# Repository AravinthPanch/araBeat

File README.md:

# araBeat

araBeat is an interactive new media art developed for the artistic sonification of Electrocardiogram (ECG). It is a complete system that consists of modules of ECG, DSP, MCU & Motherboard.

araBeat captures ECG of human Interactors through two gel-less electrodes, identifies the QRS complex of ECG, calculates the time difference between the R wave peaks and using Audio DSP, it synthesizes high & low frequency sound in realtime, which is synchronized with the heartbeats of the Interactor.

araBeat lies in the spectrum of new media art, the form of interaction with the technology is designed with aesthetics in mind using stainless steel electrodes in the form of human hand.

araBeat is designed to be extendable using modular designs, so that every component can be just individually plugged into the motherboard. It is also built as an industrial grade system to operate in harsh weather conditions from -40 ° Celsius to 85 ° Celsius. Furthermore, it is designed to comply with medical grade electronics to have low electrical noises and safety.

In the first public appearance, araBeat is integrated into a permanent & public mosaic art installation called "The Heart Of Uptown", located at MoZaic East, Minneapolis, USA.

<p align="center">
<b>The Heart Of Uptown powered by araBeat</b>
</br>
</br>

</p>

## ARTISTS

-   Aravinth Panch &lt; <http://aravinth.info> > New Media Art
-   Stacia Goodman &lt; <http://www.staciagoodmanmosaics.com> > Mosaic Art

## COLLABORATORS

-   Marc Basara - Project Management, Minneapolis
-   Stuart Ackerberg - Art Producer, Minneapolis
-   Felix Christmann - Industrial Design, Berlin
-   Alessandro Aresta - Sound Engineering, Berlin
-   Len Goodman - Graphic Design, Minneapolis
-   John Bean, Giam Nguyen, Hart Johnson, Randi Johnson - Production Management, Minneapolis
-   Pavel Spieker, Kelly Ludeking, Anthony Kling - Structural Design & Construction, Minneapolis
-   Shresth Agrawal - Software Engineering, Berlin
-   Chris Kooper - Metalworking, Berlin

## SUPPORTERS

-   Natalia Aravinth, Mladen Miljic, Darina Onoprienko - Family & Mental Support
-   David Riding, Jasmin Skenderi - Electrical Design Review, Next Big Thing, Berlin
-   Karissa Xie, Rolin Pei - CNC Machining, HLH Prototypes, Shenzhen
-   Monica Shen, Ivy Li, Carmen Zheng - PCB Manufacturing, Seeed Studio, Shenzhen
-   Goran, Sascha Hamacher - WaterJet Cutting, S-Hamacher Art Production Studio, Berlin
-   Robert Blowsky - Digital Signal Processing, Analog Devices, EZ Forum

## STUDIOS AND MANUFACTURERS

-   nLab, Berlin - Interaction Technology Design & Development
-   MotionLab, Berlin - Prototype CNC Machining
-   Tivoli Too, Minneapolis - Structural Design & Construction
-   Seeed Studio, Shenzhen - PCB Manufacturing
-   Troublemaker, Shenzhen - Prototyping
-   HLH Prototypes, Shenzhen - CNC Machining
-   S-Hamacher Art Production Studio, Berlin - WaterJet Cutting & Metalworking

## DESIGN

### Interaction Technology & Mosaic Installation Concept

## DEVELOPMENT

### The Heart Of Uptown Installation

-   #### Stage 1 Completion

-   #### Stage 2 Completion

-   #### Stage 3 Completion

### Interaction Technology

-   #### Wiring Design

-   #### Prototype v1.0

-   #### Prototype v2.0

-   #### Prototype v3.0

-   #### Prototype v4.0

-   #### Motherboard v0.1

<p align="center">

</br>

</p>

-   #### ECG Module v0.1

-   #### ECG Module v0.2

-   #### MCU Module v0.1

-   #### Motherboard v1.0

<p align="center">

</br>

</p>

-   #### Motherboard v1.0 in Weatherproof Industrial Heated Enclosure

### Sensor Frontend

-   #### Design

-   #### Prototype

-   #### Sensor Frontend v1.0

#### Marine Standard Tweeter, Sub-Woofer, Amplifier, PSU

#### Electronics & Audio Chambers

## DESIGN & DEVELOPMENT TOOLS

-   #### KiCad v5.0.1-3 for PCB Design

-   #### Atom v1.34.0 + Platform IO v4.0.0a3 for ECG Firmware Development

-   #### Fusion 360 v2.0.5357 for Mechanical Design

-   #### Rhino + Grasshoper for Surface Design

-   #### Affinity Designer v1.6.1 for Vector Design

-   #### SigmaStudio v4.2 for Audio Synthesis

-   #### Processing v3.5.3 for araBeat GUI Software Development

-   #### araBeat GUI v0.9 for Optimisation of ECG and Audio Waveforms

## The Making - Behind the scenes

-   #### Aravinth - Prototype CNC Milling at MotionLab, Berlin

-   #### Stacia - Mosaic Making at Private Studio, Minneapolis

-   #### Stacia - Mosaic Making at Private Studio, Minneapolis

-   #### Len - Structural Construction at Tivoli Too, Minneapolis

-   #### Stacia - Styrofoam + Fibreglass Surface Finish at Tivoli Too, Minneapolis

-   #### Len - Mosaic Finish at Tivoli Too, Minneapolis

-   #### Alessandro - Sound Design at Private Studio, Berlin

-   #### Chris - Metalworking at S-Hamacher Art Production Studio, Berlin

-   #### Pavel - Metalworking at Tivoli Too, Minneapolis

-   #### Kelly - Metalworking at Tivoli Too, Minneapolis

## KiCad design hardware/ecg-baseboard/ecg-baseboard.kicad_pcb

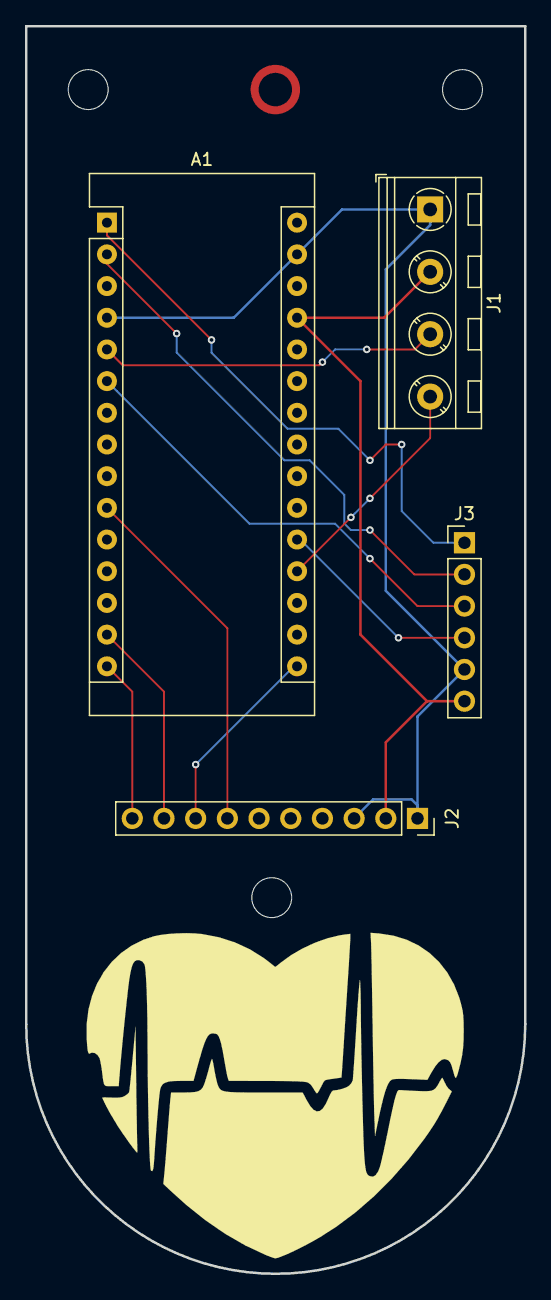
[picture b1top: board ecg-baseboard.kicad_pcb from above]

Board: 2 copper layers, 40.0 x 100.0 mm, 4 parts (0 on the bottom side), 12 nets.

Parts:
A1: Arduino_Nano_v3.x; Arduino_Nano
J1: Screw_Terminal_01x04; TerminalBlock_RND_205-00047_1x04_P5.00mm_Horizontal
J2: Protocentral MAX30003; PinSocket_1x10_P2.54mm_Vertical
J3: Conn_01x06; PinHeader_1x06_P2.54mm_Vertical

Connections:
/VCC: A1.27, J1.2, J2.2, J3.6
GND: A1.4, A1.29, J1.1, J2.1, J2.3, J3.5
unnamed: A1.1, J3.1
unnamed: A1.2, J3.2
unnamed: A1.5, J1.3
unnamed: A1.6, J3.3
unnamed: A1.10, J2.7
unnamed: A1.14, J2.9
unnamed: A1.15, J2.10
unnamed: A1.16, J2.8
unnamed: A1.19, J1.4
unnamed: A1.20, J3.4

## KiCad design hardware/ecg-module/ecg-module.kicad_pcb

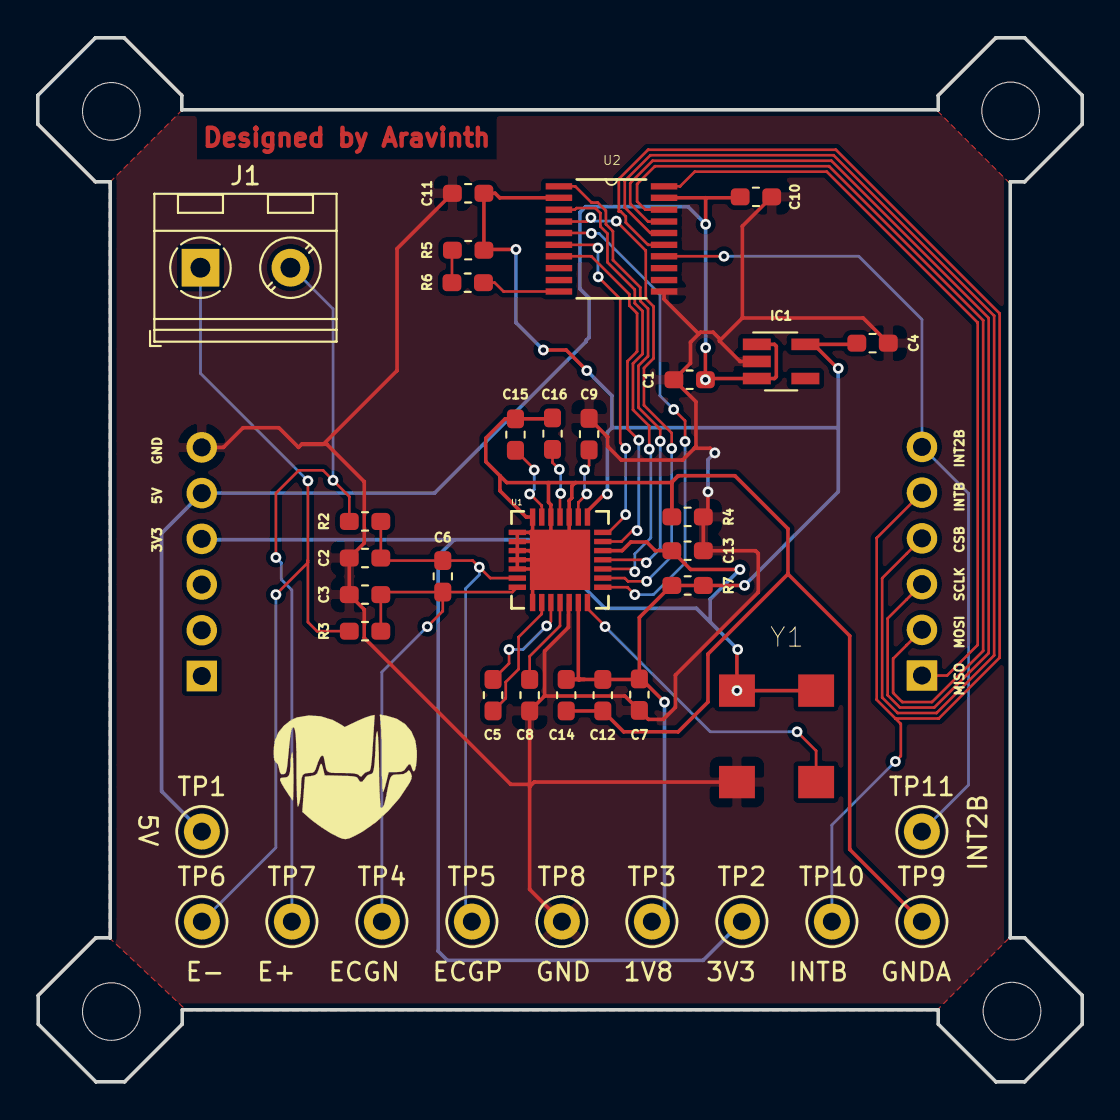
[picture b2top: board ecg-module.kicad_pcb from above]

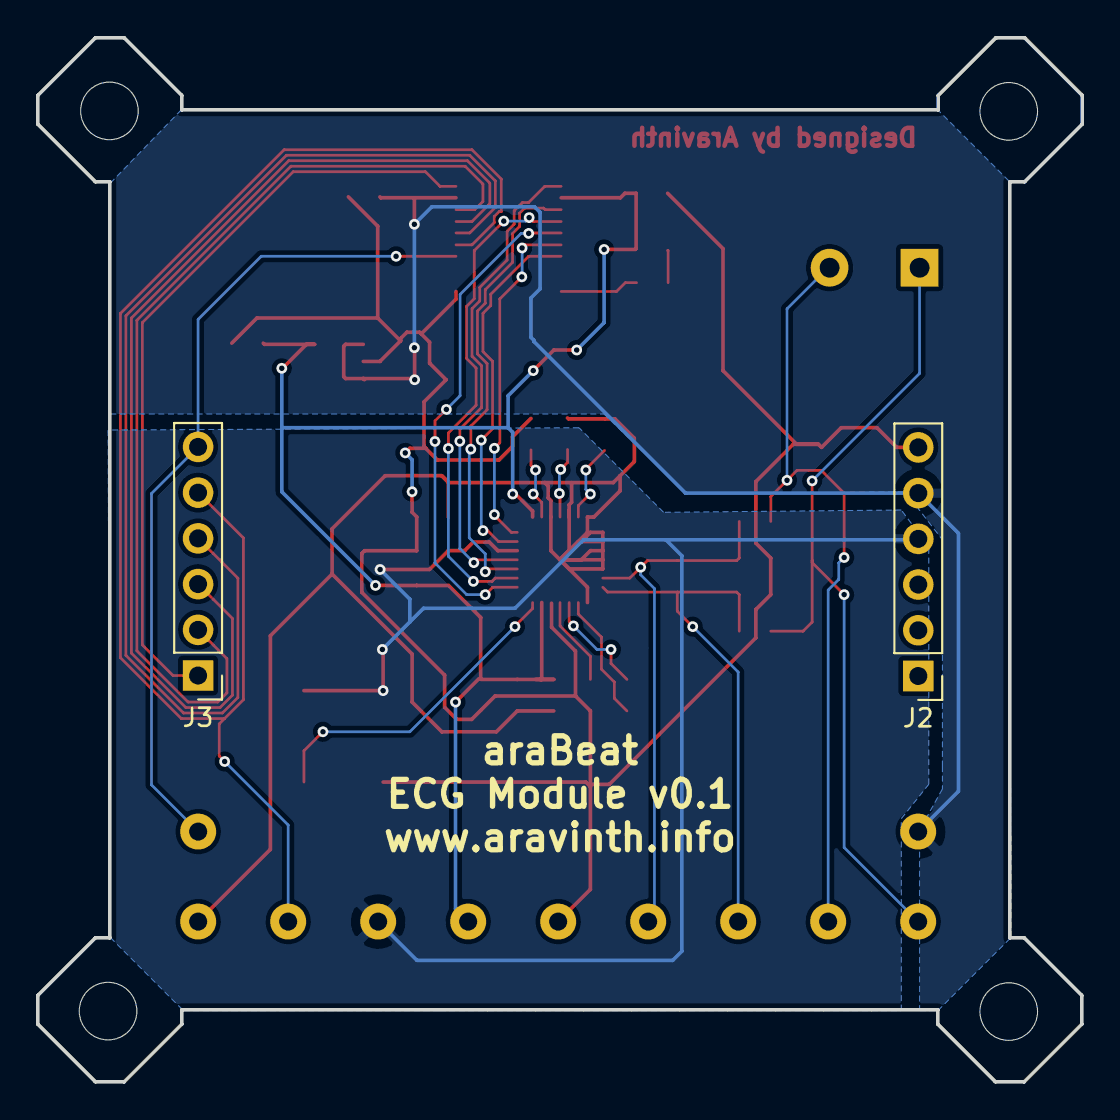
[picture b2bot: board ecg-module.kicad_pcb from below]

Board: 2 copper layers, 58.0 x 58.0 mm, 40 parts (2 on the bottom side), 30 nets.

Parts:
C1, C4, C5, C7, C12, C15: 1uF; C_0603_1608Metric_Pad1.05x0.95mm_HandSolder
C2, C3: 10pF; C_0603_1608Metric_Pad1.05x0.95mm_HandSolder
C6, C8: 1000pF; C_0603_1608Metric_Pad1.05x0.95mm_HandSolder
C9, C13, C16: 10uF; C_0603_1608Metric_Pad1.05x0.95mm_HandSolder
C10, C11, C14: 0.1uF; C_0603_1608Metric_Pad1.05x0.95mm_HandSolder
IC1: AP2112K-1.8TRG1; SOT-23-5_HandSoldering
J1: ST_01x02; TerminalBlock_RND_205-00045_1x02_P5.00mm_Horizontal
J2: LEFT-UI; PinHeader_1x06_P2.54mm_Vertical
J3: RIGHT-UI; PinHeader_1x06_P2.54mm_Vertical
R2, R3: 49.9K; R_0603_1608Metric_Pad1.05x0.95mm_HandSolder
R4, R5, R7: 0R; R_0603_1608Metric_Pad1.05x0.95mm_HandSolder
R6: 10K; R_0603_1608Metric_Pad1.05x0.95mm_HandSolder
TP1: 5V; TestPoint_Keystone_5000-5004_Miniature
TP2: 3V3; TestPoint_Keystone_5000-5004_Miniature
TP3: 1V8; TestPoint_Keystone_5000-5004_Miniature
TP4: ECGN; TestPoint_Keystone_5000-5004_Miniature
TP5: ECGP; TestPoint_Keystone_5000-5004_Miniature
TP6: E-; TestPoint_Keystone_5000-5004_Miniature
TP7: E+; TestPoint_Keystone_5000-5004_Miniature
TP8: GND; TestPoint_Keystone_5000-5004_Miniature
TP9: GNDA; TestPoint_Keystone_5000-5004_Miniature
TP10: INTB; TestPoint_Keystone_5000-5004_Miniature
TP11: INT2B; TestPoint_Keystone_5000-5004_Miniature
U1: 21-0140L_T2855-8
U2: SOP65P640X120-20N
Y1: OSCSC508P500X700X155-4N

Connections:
+1V8: C4.1, C7.1, C11.2, C12.1, C14.1, IC1.5, R5.2, R7.1, R7.2, TP3.1, U1.13, U1.22, U2.2
+3V3: C13.1, J2.4, TP2.1, U1.19, Y1.1, Y1.4
+5V: C1.1, C10.2, IC1.1, IC1.3, J2.5, TP1.1, U2.19
CSB_1.8V: U1.15, U2.5
CSB_5V: J3.4, U2.16
GND: C1.2, C2.1, C3.2, C4.2, C7.2, C8.2, C9.2, C10.1, C11.1, C13.2, IC1.2, J2.6, R4.2, TP8.1, U1.12, U2.11, Y1.2
GNDA: C12.2, C14.2, C15.2, C16.2, R4.1, TP9.1, U1.1, U1.2, U1.3, U1.4, U1.5, U1.8, U1.24, U1.26, U1.28, U1.29
INT2B_1.8V: U1.20, U2.7
INT2B_5V: J3.6, TP11.1, U2.14
INTB_1.8V: U1.21, U2.6
INTB_5V: J3.5, TP10.1, U2.15
MISO_1.8V: U1.18, U2.1
MISO_5V: J3.1, U2.20
MOSI_1.8V: U1.17, U2.3
MOSI_5V: J3.2, U2.18
unnamed: C2.2, C6.2, R2.1, TP5.1, U1.6
unnamed: C3.1, C6.1, R3.1, TP4.1, U1.7
unnamed: C5.1, U1.9
unnamed: C5.2, U1.10
unnamed: C8.1, U1.11
unnamed: C9.1, U1.23
unnamed: C15.1, U1.27
unnamed: C16.1, U1.25
unnamed: J1.1, R3.2, TP6.1
unnamed: J1.2, R2.2, TP7.1
unnamed: R5.1, R6.2
unnamed: R6.1, U2.10
unnamed: U1.14, Y1.3
SCLK_1.8V: U1.16, U2.4
SCLK_5V: J3.3, U2.17

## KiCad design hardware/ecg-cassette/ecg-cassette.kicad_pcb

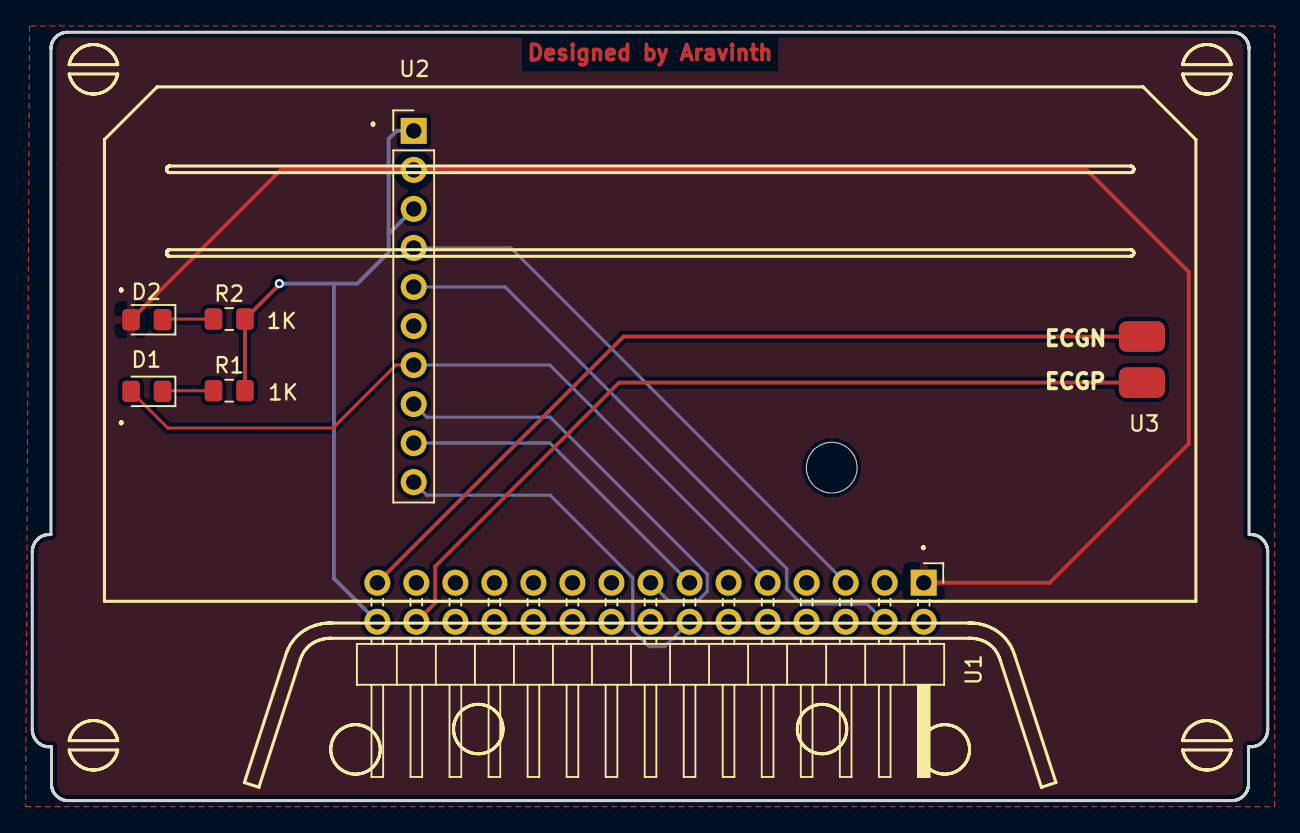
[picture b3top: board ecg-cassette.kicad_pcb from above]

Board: 2 copper layers, 80.4 x 50.0 mm, 9 parts (0 on the bottom side), 12 nets.

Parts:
D1: RED_STATUS_LED; LED_0805_2012Metric_Pad1.15x1.40mm_HandSolder
D2: GREEN_PWR_LED; LED_0805_2012Metric_Pad1.15x1.40mm_HandSolder
MARK: CASSETTE-MARK; MCU-CASSETTE-MARK
R1, R2: 1K; R_0805_2012Metric_Pad1.15x1.40mm_HandSolder
SILK: CASSETTE-SILKSCREEN; ECG-CASSETTE-SILKSCREEN-EDGECUT
U1: 02x15_PIN_HEADER_SOCKET; PinHeader_2x15_P2.54mm_Horizontal
U2: MAX30003
U3: ECG-WIRE-TO-BOARD

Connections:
5V: D2.2, U1.1, U2.2
D2: U1.4, U2.5
D3: U1.5, U2.4
D7: D1.2, U1.9, U2.7
D11: U1.13, U2.9
D12: U1.14, U2.10
D13: U1.15, U2.8
ECGN: U1.29, U3.1
ECGP: U1.28, U3.2
GND: R1.2, R2.2, U1.30, U2.1, U2.3
unnamed: D1.1, R1.1
unnamed: D2.1, R2.1

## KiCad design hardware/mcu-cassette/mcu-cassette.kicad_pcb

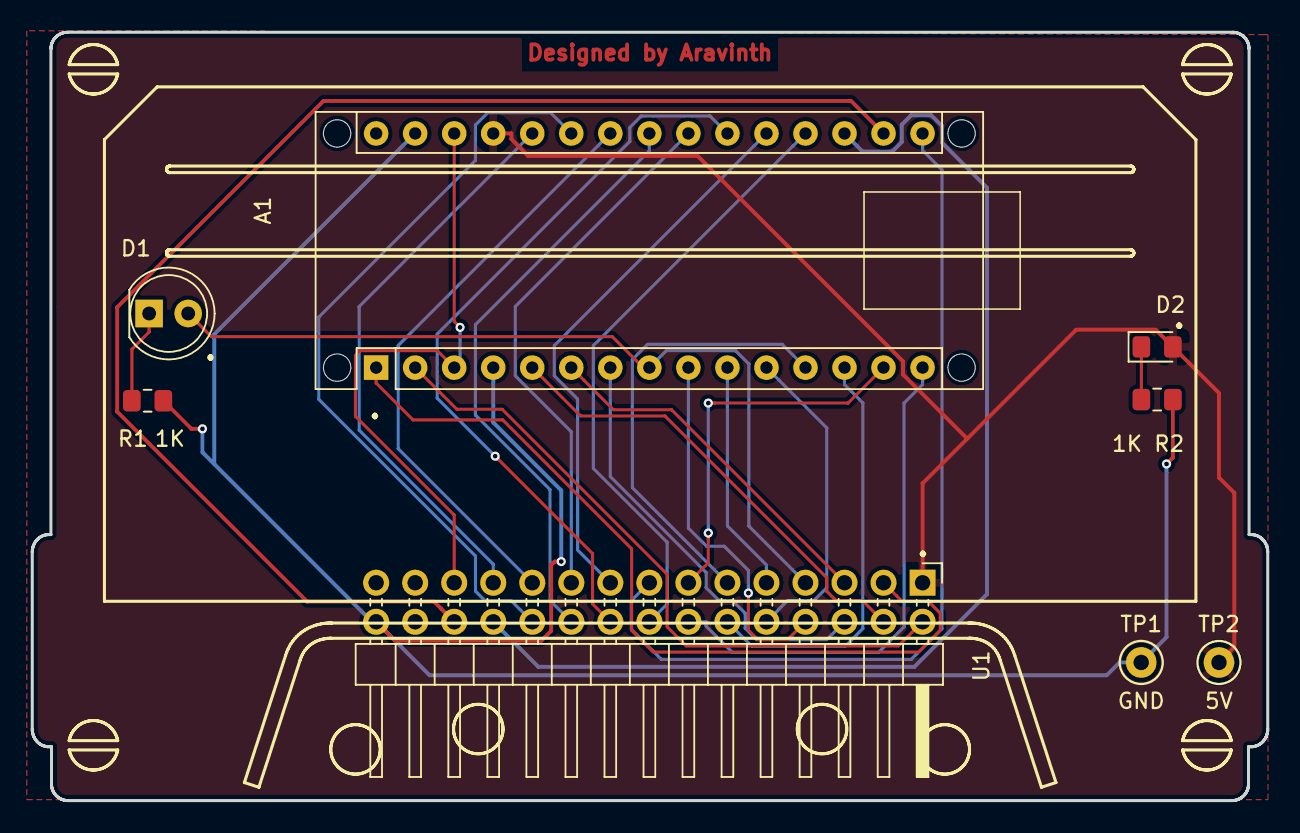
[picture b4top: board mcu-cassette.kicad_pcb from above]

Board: 2 copper layers, 80.4 x 50.0 mm, 10 parts (0 on the bottom side), 29 nets.

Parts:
A1: Arduino_Nano_v3.x; Arduino_Nano_WithMountingHoles
D1: RED_HEART_LED; LED_D5.0mm
D2: GREEN_PWR_LED; LED_0805_2012Metric_Pad1.15x1.40mm_HandSolder
R1, R2: 1K; R_0805_2012Metric_Pad1.15x1.40mm_HandSolder
SLK-FR: CASSETTE-SILKSCREEN; MCU-CASSETTE-SILKSCREEN-EDGECUT
SLK-MK: CASSETTE-MARK; MCU-CASSETTE-MARK
TP1: GND; TestPoint_Keystone_5000-5004_Miniature
TP2: 5V; TestPoint_Keystone_5000-5004_Miniature
U1: 02x15_PIN_HEADER_SOCKET; PinHeader_2x15_P2.54mm_Horizontal

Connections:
3V3: A1.17, U1.26
5V: A1.27, D2.2, TP2.1, U1.1
A0: A1.19, U1.16
A1: A1.20, U1.17
A2: A1.21, U1.18
A3: A1.22, U1.19
A4: A1.23, U1.20
A5: A1.24, U1.21
A6: A1.25, U1.22
A7: A1.26, U1.23
AREF: A1.18, U1.24
D0: A1.2, U1.2
D1: A1.1, U1.3
D2: A1.5, U1.4
D3: A1.6, U1.5
D4: A1.7, U1.6
D5: A1.8, D1.2, U1.7
D6: A1.9, U1.8
D7: A1.10, U1.9
D8: A1.11, U1.10
D9: A1.12, U1.11
D10: A1.13, U1.12
D11: A1.14, U1.13
D12: A1.15, U1.14
D13: A1.16, U1.15
GND: A1.4, A1.29, R1.2, R2.2, TP1.1, U1.30
unnamed: D1.1, R1.1
unnamed: D2.1, R2.1
RST: A1.3, A1.28, U1.25

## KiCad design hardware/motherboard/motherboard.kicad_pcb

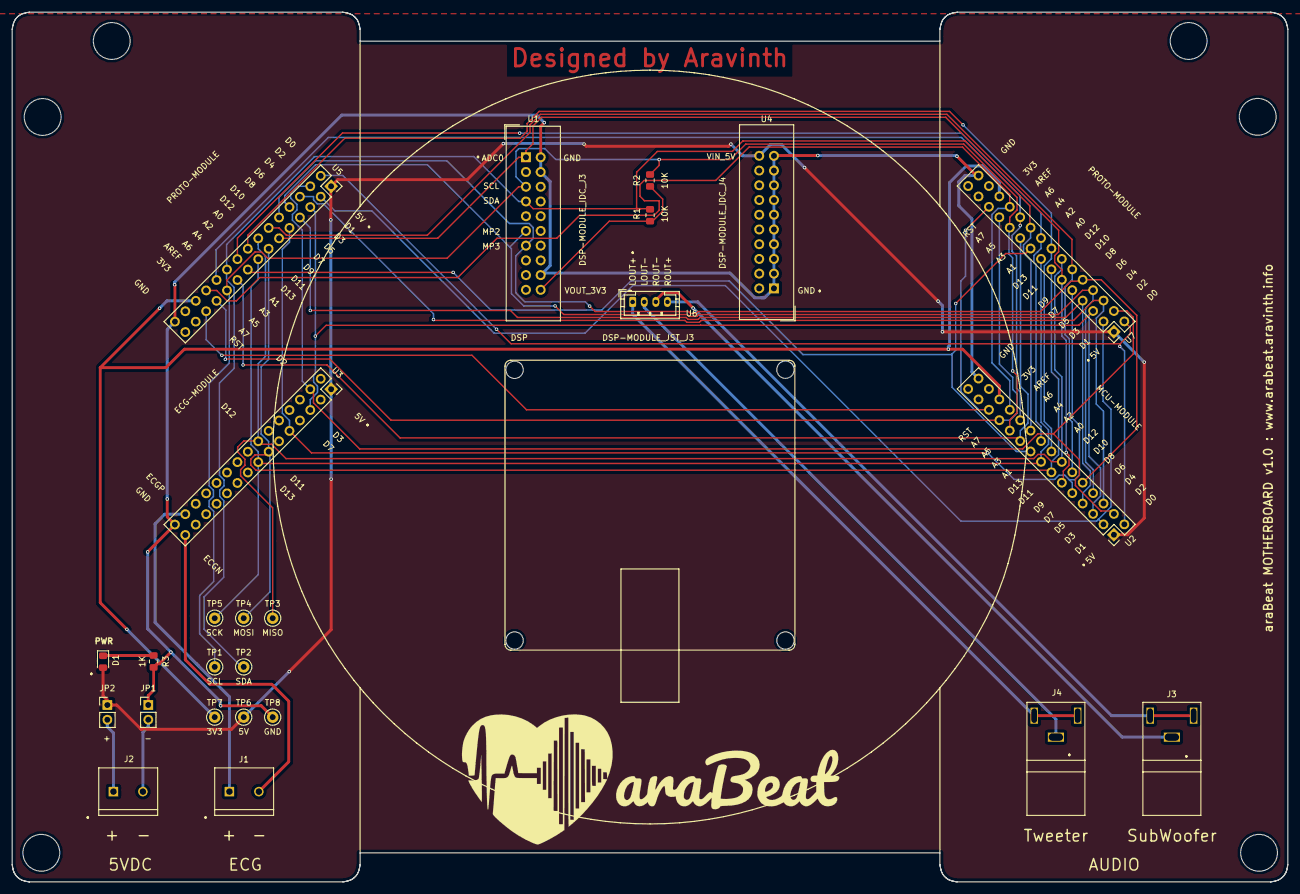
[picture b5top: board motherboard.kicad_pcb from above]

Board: 2 copper layers, 220.0 x 150.0 mm, 27 parts (0 on the bottom side), 37 nets.

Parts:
D1: GREEN_PWR_LED; LED_0805_2012Metric_Pad1.15x1.40mm_HandSolder
DSP: WONDOM-DSP
J1: 01x02_Screw_ECG; 282837-2
J2: 01x02_Screw_5VDC_IN; 282837-2
J3: RCA_L_Female_Tweeter; PJRAN1X1U01X
J4: RCA_R_Female_Sub; PJRAN1X1U01X
JP1: GND_Jumper; 382811-8
JP2: 5V_Jumper; 382811-8
MOTHERBOARD: MOTHERBOARD-SILKSCREEN-EDGECUT-MARK
R1, R2: 10K; R_0805_2012Metric_Pad1.15x1.40mm_HandSolder
R3: 1K; R_0805_2012Metric_Pad1.15x1.40mm_HandSolder
TP1: SCL; TestPoint_Keystone_5000-5004_Miniature
TP2: SDA; TestPoint_Keystone_5000-5004_Miniature
TP3: MISO; TestPoint_Keystone_5000-5004_Miniature
TP4: MOSI; TestPoint_Keystone_5000-5004_Miniature
TP5: SCK; TestPoint_Keystone_5000-5004_Miniature
TP6: 5V; TestPoint_Keystone_5000-5004_Miniature
TP7: 3V3; TestPoint_Keystone_5000-5004_Miniature
TP8: GND; TestPoint_Keystone_5000-5004_Miniature
U1: DSP-MODULE_IDC_J3; IDC-Header_2x10_P2.54mm_Vertical
U2: MCU-MODULE; PinSocket_2x15_P2.54mm_Vertical
U3: ECG-MODULE; PinSocket_2x15_P2.54mm_Vertical
U4: DSP-MODULE_IDC_J4; IDC-Header_2x10_P2.54mm_Vertical
U5, U7: PROTO-MODULE; PinSocket_2x15_P2.54mm_Vertical
U6: DSP-MODULE_JST_J3; JST_PH_B4B-PH-K_1x04_P2.00mm_Vertical

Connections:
3V3: TP7.1, U2.26, U5.26, U7.26
5V: D1.2, JP2.1, TP6.1, U2.1, U3.1, U4.20, U5.1, U7.1
A0: U2.16, U5.16, U7.16
A1: U2.17, U5.17, U7.17
A2: U2.18, U5.18, U7.18
A3: U2.19, U5.19, U7.19
A4: R1.2, TP2.1, U1.7, U2.20, U5.20, U7.20
A5: R2.2, TP1.1, U1.5, U2.21, U5.21, U7.21
A6: U2.22, U5.22, U7.22
A7: U2.23, U5.23, U7.23
AREF: U2.24, U5.24, U7.24
D0: U2.2, U5.2, U7.2
D1: U2.3, U5.3, U7.3
D2: U2.4, U3.4, U5.4, U7.4
D3: U2.5, U3.5, U5.5, U7.5
D4: U2.6, U5.6, U7.6
D5: U2.7, U5.7, U7.7
D6: U1.11, U2.8, U5.8, U7.8
D7: U2.9, U3.9, U5.9, U7.9
D8: U1.13, U2.10, U5.10, U7.10
D9: U1.1, U2.11, U5.11, U7.11
D10: U2.12, U5.12, U7.12
D11: TP4.1, U2.13, U3.13, U5.13, U7.13
D12: TP3.1, U2.14, U3.14, U5.14, U7.14
D13: TP5.1, U2.15, U3.15, U5.15, U7.15
ECGN: J1.2, U3.29
ECGP: J1.1, U3.28
GND: JP1.1, R3.2, TP8.1, U1.2, U1.4, U1.18, U2.30, U3.30, U4.1, U4.3, U4.5, U4.7, U4.9, U4.11, U4.13, U4.15, U4.17, U4.19, U5.30, U7.30
LOUT+: J4.2, J4.3, U6.1
LOUT-: J4.1, U6.2
unnamed: D1.1, R3.1
unnamed: J2.1, JP2.2
unnamed: J2.2, JP1.2
unnamed: R1.1, R2.1, U1.20
ROUT+: J3.2, J3.3, U6.4
ROUT-: J3.1, U6.3
RST: U2.25, U5.25, U7.25

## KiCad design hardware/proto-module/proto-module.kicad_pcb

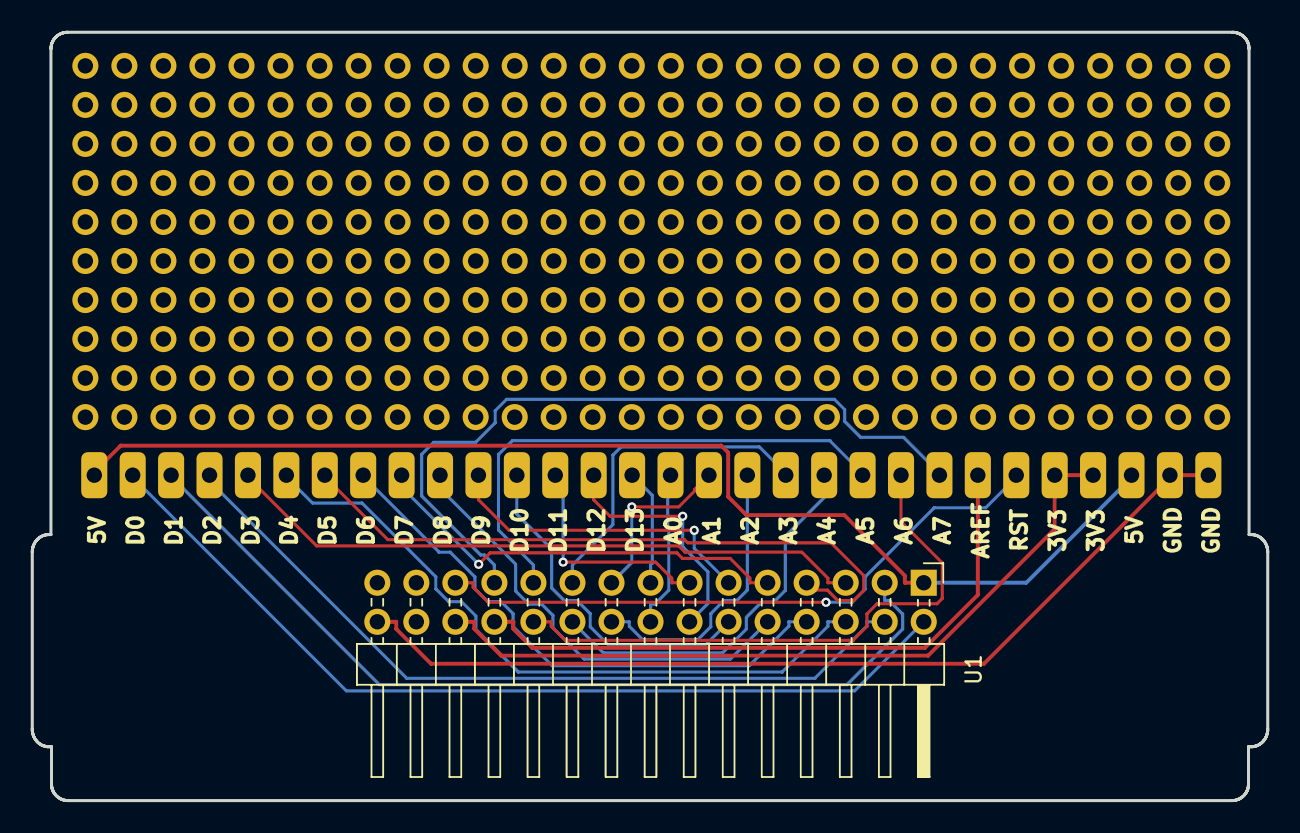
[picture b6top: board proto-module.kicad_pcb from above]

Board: 2 copper layers, 80.4 x 50.0 mm, 3 parts (0 on the bottom side), 27 nets.

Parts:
J1: Conn_01x30; PERF-PADS
PERF: PERF-BOARD
U1: 02x15_PIN_HEADER_SOCKET; PinHeader_2x15_P2.54mm_Horizontal

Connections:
3V3: J1.26, J1.27, U1.26
5V: J1.1, J1.28, U1.1
A0: J1.16, U1.16
A1: J1.17, U1.17
A2: J1.18, U1.18
A3: J1.19, U1.19
A4: J1.20, U1.20
A5: J1.21, U1.21
A6: J1.22, U1.22
A7: J1.23, U1.23
AREF: J1.24, U1.24
D0: J1.2, U1.2
D1: J1.3, U1.3
D2: J1.4, U1.4
D3: J1.5, U1.5
D4: J1.6, U1.6
D5: J1.7, U1.7
D6: J1.8, U1.8
D7: J1.9, U1.9
D8: J1.10, U1.10
D9: J1.11, U1.11
D10: J1.12, U1.12
D11: J1.13, U1.13
D12: J1.14, U1.14
D13: J1.15, U1.15
GND: J1.29, J1.30, U1.30
RST: J1.25, U1.25

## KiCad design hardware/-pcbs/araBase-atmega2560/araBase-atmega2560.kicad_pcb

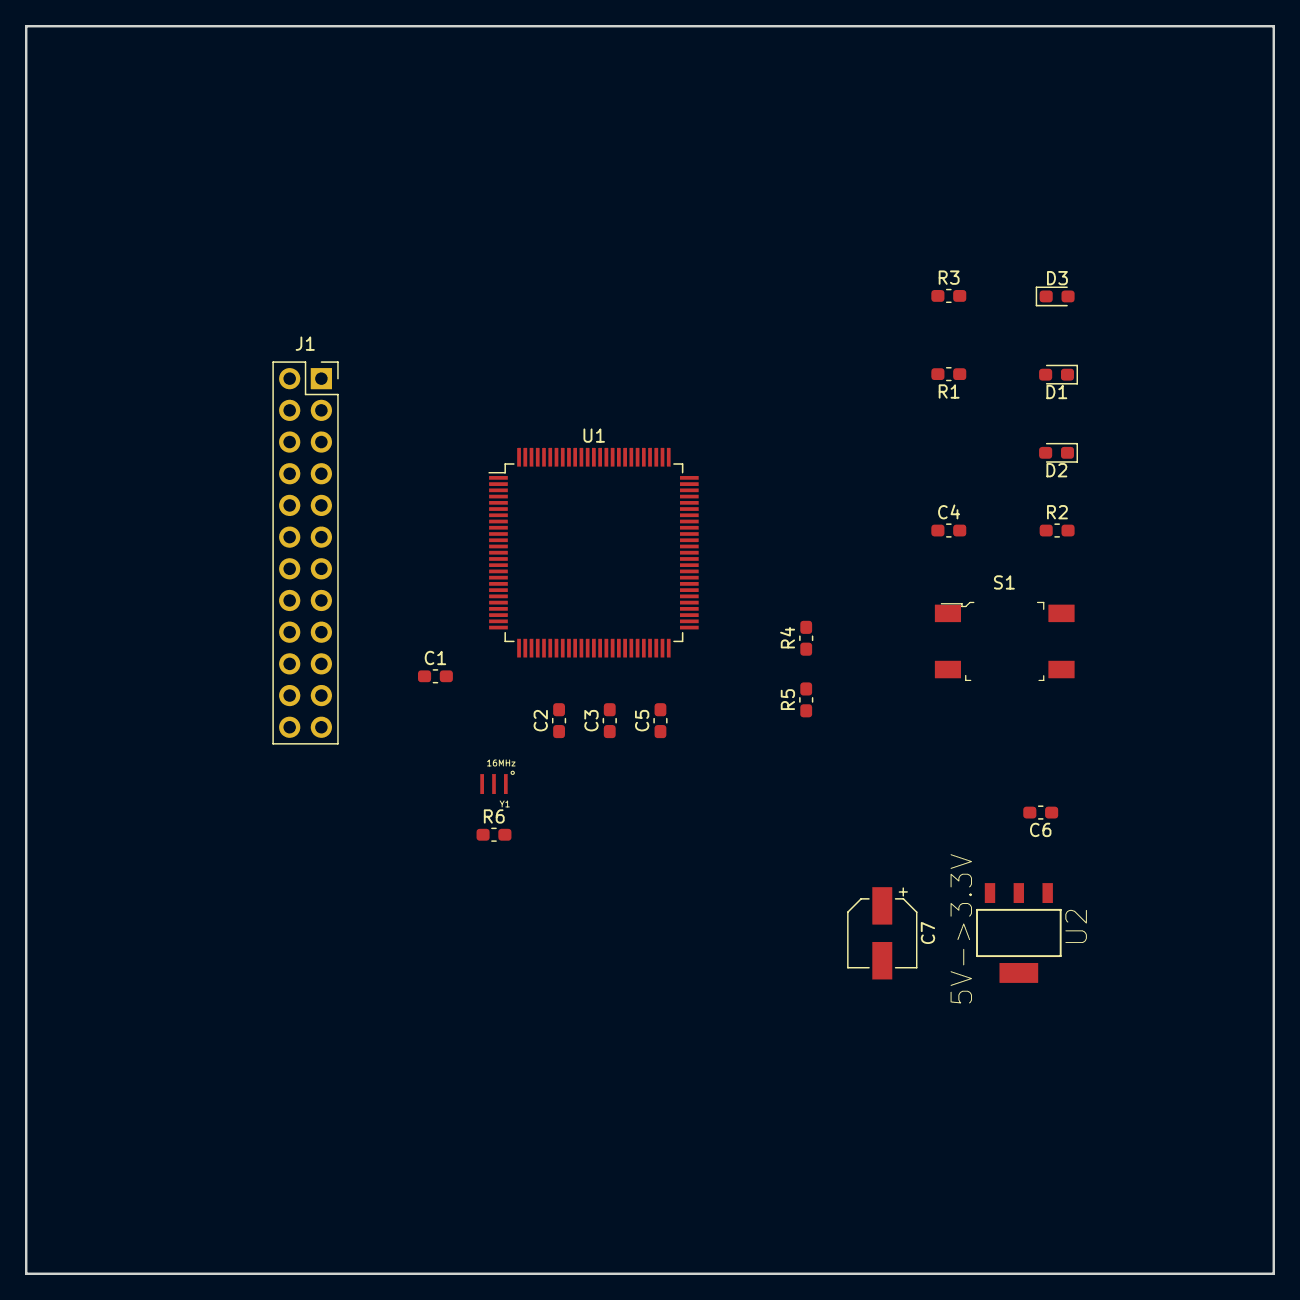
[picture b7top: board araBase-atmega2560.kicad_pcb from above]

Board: 2 copper layers, 100.0 x 100.0 mm, 21 parts (0 on the bottom side), 30 nets, no tracks yet.

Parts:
C1, C2, C3, C5: 0.1uF; C_0603_1608Metric_Pad1.05x0.95mm_HandSolder
C4: 22pF; C_0603_1608Metric_Pad1.05x0.95mm_HandSolder
C6: 100nF; C_0603_1608Metric_Pad1.05x0.95mm_HandSolder
C7: 33uF; CP_Elec_5x5.8
D1: LED-Y; LED_0603_1608Metric_Pad1.05x0.95mm_HandSolder
D2: 100V; D_0603_1608Metric_Pad1.05x0.95mm_HandSolder
D3: LED-G; LED_0603_1608Metric_Pad1.05x0.95mm_HandSolder
J1: UI; PinSocket_2x12_P2.54mm_Vertical
R1, R2, R3, R4, R5: 10K; R_0603_1608Metric_Pad1.05x0.95mm_HandSolder
R6: 1M; R_0603_1608Metric_Pad1.05x0.95mm_HandSolder
S1: RESET-SW; Switch_Tactile_SMD_6x6mm
U1: ATmega2560-16AU; TQFP-100_14x14mm_P0.5mm
U2: 5V->3.3V; SOT230P696X180-4N
Y1: 16MHz; OSC_CSTCE16M0V53-R0

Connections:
+5V: C2.1, C3.1, C5.1, C6.1, D2.1, J1.1, R2.2, R3.1, R4.2, R5.2, U1.10, U1.31, U1.61, U1.80, U1.100, U2.1
/3.3V: C7.1, J1.3, U2.3
/A0: J1.13, U1.97
/A1: J1.14, U1.96
/A2: J1.15, U1.95
/A3: J1.16, U1.94
/A4: J1.17, U1.93
/A5: J1.18, U1.92
/AREF: C1.1, J1.12, U1.98
/D2: J1.19, U1.6
/D3: J1.20, U1.7
/D4: J1.21, U1.1
/D5: J1.22, U1.5
/D6: J1.23, U1.15
/D7: J1.24, U1.16
/MISO: J1.6, U1.22
/MOSI: J1.7, U1.21
/RESET: C4.1, D2.2, J1.4, R2.1
/RX0: J1.9, U1.2
/SCK: J1.5, U1.20
/SCL: J1.11, R4.1, U1.43
/SDA: J1.10, R5.1, U1.44
/TX0: J1.8, U1.3
GND: C1.2, C2.2, C3.2, C4.2, C5.2, C6.2, C7.2, D1.1, D3.1, J1.2, S1.1, S1.2, U1.11, U1.32, U1.62, U1.81, U1.99, U2.2, U2.4, Y1.2
unnamed: D1.2, R1.2
unnamed: D3.2, R3.2
unnamed: R1.1, U1.13
unnamed: R6.1, U1.33, Y1.3
unnamed: R6.2, U1.34, Y1.1
unnamed: S1.3, S1.4, U1.30

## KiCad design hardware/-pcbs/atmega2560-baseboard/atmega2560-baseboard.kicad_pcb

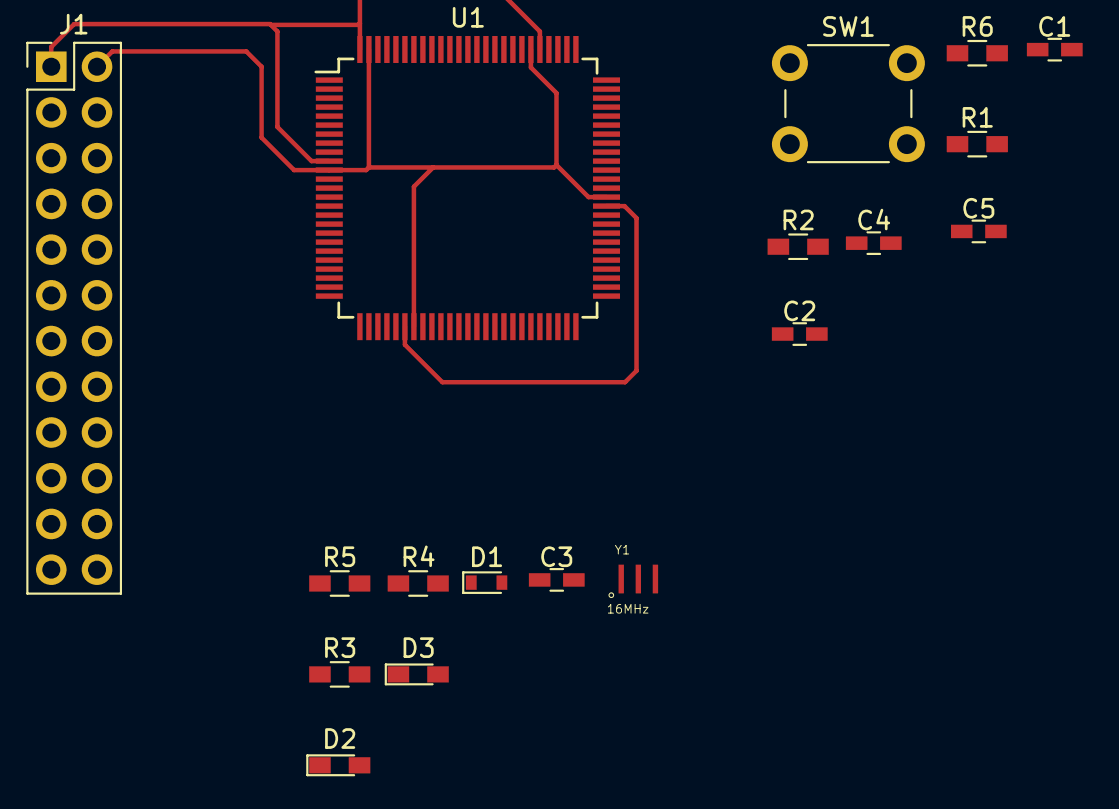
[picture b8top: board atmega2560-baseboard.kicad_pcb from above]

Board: 2 copper layers, 18 parts (0 on the bottom side), 28 nets.

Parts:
C1: 0.1uf; C_0603_HandSoldering
C2, C3, C5: 0.1uF; C_0603_HandSoldering
C4: 22p; C_0603_HandSoldering
D1: D; D_0603
D2, D3: LED; LED_0603_HandSoldering
J1: Bottom; Pin_Header_Straight_2x12_Pitch2.54mm
R1, R2, R3, R4, R5: 10K; R_0603_HandSoldering
R6: 1M; R_0603_HandSoldering
SW1: SW_Push; SW_PUSH_6mm
U1: ATMEGA2560-16AU; TQFP-100_14x14mm_Pitch0.5mm
Y1: 16MHz; OSC_CSTCE16M0V53-R0

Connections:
+5V: C2.1, C3.1, C5.1, D1.1, J1.1, R1.1, R2.1, R3.2, R5.2, U1.10, U1.31, U1.61, U1.80, U1.100
/A0: J1.19, U1.97
/A1: J1.20, U1.96
/A2: J1.21, U1.95
/A3: J1.22, U1.94
/A4: J1.23, U1.93
/A5: J1.24, U1.92
/AREF: C1.1, J1.12, U1.98
/D2: J1.13, U1.6
/D3: J1.14, U1.7
/D4: J1.15, U1.1
/D5: J1.16, U1.5
/D6: J1.17, U1.15
/D7: J1.18, U1.16
/D13: R4.2, U1.13
/MISO: J1.6, U1.22
/MOSI: J1.7, U1.21
/RESET: C4.1, D1.2, J1.4, R3.1, SW1.1, U1.30
/RX0: J1.9, U1.2
/SCK: J1.5, U1.20
/SCL: J1.11, R1.2, U1.43
/SDA: J1.10, R2.2, U1.44
/TX0: J1.8, U1.3
/XTAL1: U1.34, Y1.1
/XTAL2: U1.33, Y1.3
GND: C1.2, C2.2, C3.2, C4.2, C5.2, D2.1, D3.1, J1.2, SW1.2, U1.11, U1.32, U1.62, U1.81, U1.99, Y1.2
unnamed: D2.2, R4.1
unnamed: D3.2, R5.1

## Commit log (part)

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2018-06-30 Add hardware resources
2018-06-30 Add firmware files
2018-06-30 Add Helge EKG visualizer
2018-06-30 Add phase 1 design and dfrobot ecg
2018-07-01 Add pcb design files, schematics and datasheets
2018-07-01 Add files of state-of-the-art in two electrode ecg
2018-07-01 Add existing projects
2018-07-03 Add default sparkfun ecg firmware
2018-07-05 Add adafruit music maker files
2018-07-05 Add music maker platform io
2018-07-06 Add bumpy mp3 project
2018-07-06 Clean files
2018-07-07 Add sparkfun mp3 shield files
2018-07-11 Add mini speaker enclosure design
2018-07-11 Add midi maker files
2018-07-11 Update mini speaker enclosure design
2018-07-11 Update midi test
2018-07-11 Add pure data to synthesize heartbeat audio
2018-07-11 Add minimal code for realtime midi output
2018-07-11 Update music maker midi for test synthesize
2018-07-15 Add enclosure results
2018-07-15 Add atmega2560 baseboard pcb
2018-07-15 Add gitignore file for kicad
2018-07-15 Add atmega datasheet
2018-07-15 Remove temp files from tracking
2018-07-15 Resize schematics and add reset line
2018-07-15 Update oscillator and reset line in schematics
2018-07-15 Add 02x12 connector strip
2018-07-16 Add pinout wiring to schematics
2018-07-16 Add annotations to schematics
2018-07-16 Add footprint assosciations
2018-07-16 Add CSTCE16M0V53-R0 crystal resonator footprint
2018-07-16 Update crystal resonator in schematics
2018-07-16 Add pcb layout file
2018-07-16 Spread out all footprints
2018-07-16 Route VCC and GND pin
2018-07-16 Route basic pins
2018-07-18 Add lpkf test pcb file
2018-07-18 Update schematics with QFN chip
2018-07-18 Route pcb
2018-07-18 Add LKPF Test min files
2018-07-22 Add ad8232 evalboard datasheet
2018-07-31 Update gitignore
2018-07-31 Archive kicad4 proects
2018-07-31 Add araBase-atmega2560 kicad5 project
2018-07-31 Add pwr flags, labels and mark unconnected pins
2018-07-31 Add LM3940 voltage regulator library
2018-08-01 Add resonator crystal footprint
2018-08-01 Update schematics and assign foot prints
2018-08-01 Setup pcb layout and Import netlist
2018-08-01 Add 100mmx100mm edge cut and distribute footprints
2018-08-01 Setup design rules for 10mil/10mil trace and 0.8mm/0.4mm via/drill
2018-10-29 Add documents
2018-10-29 Add prototype images
2018-10-29 Add maxim-30003
2018-10-29 Add ADAU1701 proto
2018-10-29 Add proto-1 files
2018-10-29 Remove pcb files, moved to various-hardware-projects repo
2018-10-29 Add max30003 repo from protocentral
2018-10-29 Add full system design files
2018-11-08 Add schematics and resources of ecg baseboard
2018-11-08 Add basic pcb layout
2018-11-08 Add silkscren text, logo, gnd copper fill, traces
2018-11-09 Add pinheader and screwterminal to the schematics
2018-11-09 Add edgecut, mounting hole and component aligments
2018-11-09 Add complete routing, copper fill, silkscreen texts, fiducials
2018-11-10 Update pcb, generate step file and image
2018-11-13 Add design files of sensor frontend
2018-11-13 Add GPIO Mux dsp patch
2018-11-13 Add protocentral repo
2018-11-14 Add footprint and symbol of LDO AP2112K-1.8TRG1, Clean files
2018-11-14 Add TXB0108PWR logic level converter symbol and footprint
2018-11-14 Add 1.8 V to 5V Logic Level Conversion schematic
2018-11-14 Update schematic
2018-11-15 Add quartz crystal, audio jack, update schematic
2018-11-15 Update analog frontend schematics
2018-11-15 Update logic level and LDO schematics
2018-11-15 Add test points
2018-11-16 Add footprint and symbol of oscillator and audio jack
2018-11-16 Add footprints association and update schematics
2018-11-17 Add footprints in the pcb layout
2018-11-17 Put footprints in right place
2018-11-19 Add GND and GNDA routing
2018-11-28 Add image files
2018-11-29 Clean files and add foam-mill images
2018-11-29 Add 3d models of organic hand design
2018-12-15 Add basic routing
2018-12-15 Update footprint to screw terminal
2018-12-15 Update routing
2018-12-15 Add motherboard reference and other files
2018-12-16 Complete all connections route
2018-12-16 Add copper pour of bottom layer
2018-12-16 Add copper pour of top layer
2018-12-16 Add ecg heart logo
2018-12-16 Clean up traces, add design label on copper
2018-12-19 Production ready
2018-12-24 Add bom file
2018-12-24 Add stl of design-3
2018-12-26 Clean files and update README
2018-12-28 Add production stainless steel sensor-frontend with 10 deg draft, 5mm shell
2018-12-28 Add datasheets
2019-01-01 Add SPI test suite for MAX30003
2019-01-08 Clean files, Add images
2019-01-08 Update protocentral repo
2019-01-09 Add system design files
2019-01-10 Update system design files
2019-01-10 Add wiring design to readme
2019-01-10 Add arabeat project logo
2019-01-10 Add protective to wiring design
2019-01-11 Add DSP patches
2019-01-11 Reduce the gain, set frequenzy to 1.2 Hz
2019-01-12 Add datasheets of audio system
2019-01-24 Add test tones of sine waves and heartbeats
2019-01-24 Add images and update README
2019-01-25 Add ecg firmware as platform.io project
2019-01-25 Clean files, add mbed MAX30003
2019-01-25 Rename header file
2019-01-25 Restructure the code into class
2019-01-26 Add basic ECG readout from max3003 for serial plotting
2019-01-26 Add arduino nano test firmware project
2019-01-26 Update spi register write function
2019-01-26 Add max30003 registers and configurations as class
2019-01-26 Update max30003 general config
2019-01-26 Update calibration and mux config
2019-01-26 Update ECG config
2019-01-26 Updat RtoR config
2019-01-26 Disable debug messages
2019-01-26 Add plot function to send to PDE GUI
2019-01-26 Add R-To-R readout
2019-01-26 Clean filename case-sensitive
2019-01-26 Clean file - filename
2019-01-27 Add ecg-proto firmware
2019-01-27 Update spi register read and ecg fifo read
2019-01-27 Add r to r readout
2019-01-27 Optimze the register settings
2019-01-27 Add interrupt driven ECG readout
2019-01-28 Add RtoR interrupt driven readout
2019-01-28 Add update reg configs, dc lead-off detection,
2019-01-28 Add RTOR led status
2019-01-28 Add function to check if the electrodes are touched
2019-01-28 Clean code
2019-01-28 Add basic electron.io app
2019-01-29 [software] Update gui with time series chart
2019-01-29 [software] Update readme, add iconset
2019-01-29 Clean code, move code base to renderer, add jquery
2019-01-29 [software] Clean code
2019-01-30 [hardware] Add enclosure design and heated-plate files
2019-01-30 [hardware] Add motherboard & module board-outline designs
2019-01-31 Rename ecg-module
2019-01-31 [hw] Clean files
2019-01-31 [hw] Add connectors images
2019-01-31 [hw] Add ECG cassette schematic, footprint, symbol, 3D models, datasheets
2019-02-02 [hw] Add routing, silkscreen, copper pour, edgecut to ecg-cassette
2019-02-02 [hw] Finish ecg module v0.2 design
2019-02-03 [hw] Add schematic, layout, datasheets, footprints, 3d models, logo of MCU module
2019-02-03 [doc] Add pcb images and update README
2019-02-03 [hw] Move copper pour to back layer, Add signature, Update pcb images
2019-02-06 Move arabeat gui app to another repo
2019-02-06 Add new logo proto
2019-02-06 [hw] Add motherboard schematics and footprints
2019-02-08 [hw] Update motherboard schematics
2019-02-12 Enable sending ASCII data to serial
2019-02-13 Add a parent project folder and migrate libraries of footprints and symbol to parent project folder,
2019-02-13 Add TE Connectivity 2x15 pin header and socket footprints and symbols
2019-02-13 Add protocentral gui app binaries in win and linux
2019-02-13 [hw] Update footprint of ECG Baseboard project
2019-02-13 [hw] Update libraries of ECG Cassette
2019-02-13 [hw] Update libraries of ECG Module
2019-02-13 [hw] Update libraries of MCU Cassette
2019-02-13 [hw] Update libraries of Motherboard
2019-02-13 [hw] Update libraries of TE Connectivity
2019-02-13 [hw] Update MCU Cassette with new footprints
2019-02-13 [hw] Update ECG Cassette with new footprints & schematics
2019-02-13 [hw] Update Motherboard with new footprints & schematics
2019-02-16 [docs] Add speaker rack images
2019-02-20 [fw] Update DSP to accept pulses from GPIO
2019-02-20 [hw] Update motherboat schematics
2019-02-20 [fw] Add DSP i2c beep test
2019-02-20 [fw] Update DSP i2c beep test
2019-02-20 [fw] Add i2c test c++ firmware
2019-02-20 [fw] Add plotting library to send data to different GUIs
2019-02-22 [fw] Add organic heart beat dsp patch
2019-02-24 [fw] Add DSP patches from KJBob & Ale
2019-02-24 [fw] Add gpio pulse test
2019-02-24 [fw] Update DSP pulse beat test patches
2019-02-24 [fw] Update DSP organic beat patch
2019-02-24 [design] Update araBeat logo
2019-02-24 [sw] Add araBeat GUI OSX app
2019-02-24 [design] Update logo
2019-02-24 [hw] Update MCU cassette schematics, layout, footprints
2019-02-24 [docs] Add images
2019-02-24 [hw] Make MCU Module production ready
2019-02-25 [hw] Make ECG Module production ready
2019-02-25 [hw] Add schematics, footprints, layout of Proto Module
2019-02-25 [hw] Make Proto Module production ready
2019-02-25 [doc] Update README
2019-02-25 [hw] Update motherboard schematics, footprints
2019-02-26 [hw] Add motherboard edgecut, silkscreen & mark designs and clean files
2019-02-26 [hw] Add footprints of JST, SWITCHCRAFT & TE-CONNECTIVITY
2019-02-26 [hw] Update proto module layout
2019-02-26 [hw] Update motherboard schematics and layout
2019-02-26 [fw] Add TE Connectivity 382811-8 footprint
2019-02-26 [hw] Add 3D models of complete ECG, MCU & PROTO modules
2019-02-26 [hw] Add footprint of Wondom DSP
2019-02-26 [hw] Add jumper, pwr led, silkscreen logo to Motherboard
2019-02-27 [hw] Add mounting hole to mother board to fit into heated enclosure
2019-02-27 [hw] Add motherboard pcb 3d file
2019-02-27 [hw] Route motherboard
2019-02-27 [hw] Add copper pour on both planes
2019-02-27 [hw] Add all silkscreen texts to motherboard
2019-02-27 [hw] Remove silkscreen text outside of edgecut
2019-02-27 [hw] Update gerber setting to enable edge-layer exclusion
2019-02-27 [hw] Make Motherboard production ready
2019-02-28 [hw] Add iBOM of production PCBs
2019-02-28 [doc] Add DFM resources, PCB image
2019-02-28 [fw] Add env for nano new bootloader
2019-02-28 [docs] Clean files
2019-02-28 [fw] Send digital output to the GUI
2019-02-28 [docs] Add images, document & 3D model of motherboard
2019-03-02 [hw] Update motherboard schematics, footprints and 3d models
2019-03-02 [hw] Update MCU module schematics, footprints, 3d models
2019-03-02 hw] Update ECU module schematics, footprints, 3d models
2019-03-02 [hw] Update ECU module v0.1 schematics, footprints, 3d models
2019-03-02 [hw] Update Motherboard v0.1 schematics, footprints, 3d models
2019-03-03 [fw] Send 2 bytes R2R value to araBeat GUI
2019-03-03 [fw] Remove delay in SPI communication
2019-03-03 [fw] Parameterise R2R prescale value
2019-03-03 [fw] Update the algorithm for reliable electrode touched detectio, clean code
2019-03-04 [fw] WIP: Synchronize ECG analog voltage and RTOR pulses
2019-03-04 [fw] Clean code
2019-03-04 [fw] Clean code, add pin configurations MCU & DSP outputs
2019-03-04 [fw] Add RTOR interrupt pulse graph output
2019-03-05 [fw] Fix heart pulse generation
2019-03-05 [fw] WIP: Add hands on detection algorithm
2019-03-06 [fw] WIP : Send fake pulses before RTOR stabilisation
2019-03-06 [doc] Add screenshots, update README
2019-03-07 [fw] Send internal parameters to GUI
2019-03-08 [fw] Add production DSP patch of Alessandro
2019-03-08 [fw] Update pin configuration and clean files
2019-03-08 [fw] Update DSP patch to current hardware configurations
2019-03-10 [docs] Add images of the development
2019-03-10 [doc] Update README, add images
2019-03-10 [doc] Add datasheet of new 5VDC PSU
2019-03-18 [doc] Add Logo poster design
2019-03-18 [hw] Remove global kicad project file
2019-03-18 [fw] Remove unwanted variables
2019-03-18 [fw] Update DSP patch with crossover LPF and HPF
2019-03-18 [fw] Clean DSP files
2019-03-18 [fw] Ignore files, update DSP patch with linked crossover
2019-03-18 [fw] Update ChimeGenerator for tone and crossover filter
2019-03-18 [sw] Add arabeat GUI v1.0 binary
2019-03-18 [fw] Update MAX30003 configs, disable DCLOFF
2019-03-18 [fw] Update the HPF, LPF corner frequency and gain for the installation
2019-03-30 [doc] Update README, clean files, add images
